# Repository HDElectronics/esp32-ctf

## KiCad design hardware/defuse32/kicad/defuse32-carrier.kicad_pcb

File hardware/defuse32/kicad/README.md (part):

# Defuse32 carrier PCB, rev 3.1 (KiCad 10, 4 layers; schematic rev 2.1)

The carrier board sits on the case floor and connects to the six plates by ribbon cables. Rev 2 is an SMD board assembled by JLCPCB: ESP32-WROOM-32E module, USB-C programming port with a CH340C, two MCP23017 expanders, LIS3DH tilt sensor, push-push microSD, WS2812 buffer, buzzer driver and one keyed IDC box header per plate. The source of truth is [`../SPEC.md`](../SPEC.md), section "Rev 2 carrier (2026-10-23)", plus the sections it keeps: ESP32 pin map, MCP23017 allocation (rev 1b), WS2812 chain, I2C addresses and the plate signal sets (rev 1 Jn_B table).

**Status (2026-11-25): rev 3.1, the standards pass of rev 3 (section "Standards pass (2026-11-25)"), with schematic rev 2.1 (Q1 SS8050, R7 330 Ω, new R21 WS_DATA pull-down and R22 SD CMD pull-up, owner-approved). Not ordered yet. Rev 3 (2026-10-24, commit 2b482c1): re-routed on 4 layers (JLCPCB JLC04161H-7628) and finished: GND pours on both outer layers stitched into two solid GND planes, 1.0 mm silkscreen beside every part (nothing on the bottom), 3D models for every part; JLCPCB fabrication and assembly files in `out/jlcpcb/`.** Rev 3 changed copper and silkscreen only (section "Rev 3"); rev 3.1 also adds R21 / R22 to the routed board (no regeneration).

| Check | Result |
|---|---|
| `kicad-cli sch erc --severity-all` | 0 errors, 0 warnings |
| `kicad-cli pcb drc --severity-all --schematic-parity --refill-zones --all-track-errors` | 0 violations, 0 unconnected items, 0 schematic parity issues (JLCPCB 4-layer minimums and custom rules; silk_over_copper, silk_overlap, silk_edge_clearance are errors; silk clearance 0.15 mm, text >= 1.0 mm / 0.15 mm) |
| `gen/check_netlist.py` | OK: netlist and board pads match `design.py`, plus the SPEC pin map, MCP23017 allocation, IDC pinout rule, rails, AMS1117 capacitors, outline, holes, U1 antenna beyond the edge and net classes |
| `gen/pcb_audit.py` (finish audit, `out/audit.json`; routing checks tightened 2026-11-25) | silkscreen: 0 violations, 0 warnings, no hidden part reference (R16-R19 share the label "R16-19"; the fiducials FID1-FID3 are board-only and print no reference); 3D: every part has a model; routing: 0 right angles, **7 jogs**, 23 tight corners, 1 hairpin, 0 cap-only joins, 0 stray segments (rev 3 by the same count: 23 / 30 / 3 / 7 / 10; every one left has its measured reason under "Standards pass"); copper: 66 narrow voids (129.3 mm2), none can take a usable stitching via |
| `gen/std_audit.py` (standards measurements, `out/std_audit.json`) | 0 off-angle segments, 0 acute junctions, 0 vias in SMD pads, every fast-net layer change within 2 mm of a GND via, LCSC on all 68 fitted parts; copper 0.5 mm or more from the two long edges (J11's shell pads 0.475 mm); 5V F1 -> U5 / U6 34 / 48 mΩ (network solve) |

Rev 1b (THT, DevKitC socket, 190 x 140 mm, routed) is in git, tag `carrier-rev1b`.

Changes against SPEC "Rev 2 carrier" made on 2026-10-23 (SPEC.md not edited yet): **U5 (3V3P) is an AMS1117-3.3** instead of the AP2112K-3.3 (see Power), and the microSD card-detect level is now documented (**low = card present**; firmware `CONFIG_D32_SD_DET_ACTIVE_HIGH=n`).

## Rev 3: four layers (2026-10-23/24)

The owner reviewed rev 2.1 and asked for: no gaps left between tracks (grounded copper), no 90° corners, 3D models for every part, labels aligned and right next to their part (R4 with R6 R9 R5; C6 and R20 beside, not off a corner), 4 layers allowed, and JLCPCB's capabilities respected (with the JLCPCB Tools plugin's conventions). Rev 3 keeps placement, schematic, netlist and pin map, and re-routes the board on 4 layers.

| | rev 2.1 (2 layers) | rev 3 (4 layers) |
|---|---|---|
| Stack-up | 2 layers, 1.6 mm | JLC04161H-7628, 1.6 mm: signals + GND pour / GND plane / GND plane / signals + GND pour |
| Jogs (audit) | 49 | **9** (110 straight out of Freerouting) |
| 90° corners (audit) | 12 | **0** |
| Copper voids >= 0.5 mm2 (audit) | 83, 159 mm2 | 60, 137.8 mm2 |
| ... of which a stitching via fits | 0 | 2 by the audit's test, neither usable (below) |
| Silkscreen violations / warnings (rev 3 audit, text >= 1.0 mm) | 3 / 18 (two 45° labels, R4 out of its row; 11 ambiguous, 7 far) | **0 / 0** |
| Reference size | 0.8 mm / 0.15 mm | 1.0 mm / 0.15 mm (JLCPCB's minimum height) |
| Top-side parts labelled on the bottom silkscreen | 7 | **0** |
| Callouts (label + leader) | 3 | 10 |
| Hidden references | none | none (R16-R19 share one label, "R16-19") |
| Parts without a 3D model | 4 (J7, SW1, SW2, F1) | **0** |
| Vias | 427 (275 GND) | 524 (353 GND: 45 fan-out, 144 island, 138 grid, 11 return, 15 pre-route) |
| Track length | 5978 mm, 1272 segments | 6116 mm (F.Cu 3243, B.Cu 2873), 1442 segments |
| USB D+ / D- | 15.6 mm (2 vias) / 14.8 mm, 0.8 mm apart | 15.4 mm (2 vias) / 14.8 mm, 0.6 mm apart, no double bend |
| Decoupling (cap pad to supply pad) | table below | unchanged, every cap within 3 mm |
| KiCad DRC (all severities, parity, refill) / ERC / check_netlist | 0 / 0 / 0, 0, OK | 0 / 0 / 0 (JLCPCB rules), 0, OK |

**Stack-up (option B of the pcb-layout-pro skill, `references/four-layer.md`).** JLCPCB JLC04161H-7628, 1.6 mm: L1 F.Cu signals + power + GND pour, L2 In1.Cu solid GND plane, L3 In2.Cu solid GND plane, L4 B.Cu signals + power + GND pour; no tracks on L2/L3. Option A (power areas on L3) was the default; B was chosen because:

- the three rails (5V, 3V3, 3V3P) each reach the whole board and meet on adjacent pins of every box header (pin 1 = 5V, pin 3 = 3V3P), so L3 cannot be split into areas; it would become a layer of 0.6 mm power tracks that crossed each other and cut the plane under every L4 signal;
- in JLC04161H-7628 L2 and L3 are 1.065 mm apart (core), so a power plane on L3 would add only ~4 pF/cm2 of plane capacitance; the decoupling caps do that job anyway;
- with B every signal layer has an unbroken GND plane 0.21 mm away and a layer change stays GND-to-GND (a GND via next to it carries the return); power currents are small (≤ 1 A on 5V), 0.6 mm tracks are plenty.

**JLCPCB rules (no extra cost).** Board minimums and the `.kicad_dru` follow JLCPCB's 4-layer capability page (read 2026-10-23, numbers in the skill's `references/jlcpcb.md`), at values that stay inside the standard price: no hole under 0.2 mm, 0.2 mm holes only with ≥ 0.45 mm vias (GND fan-out and stitching vias 0.45/0.2; signal and power vias 0.6/0.3), via hole to via hole 0.25 mm, pad hole to pad hole 0.45 mm, PTH hole to track 0.28 mm, inner PTH hole to copper 0.3 mm, track/space ≥ 0.1 mm (the net classes keep 0.2/0.2 and 0.6/0.25), copper 0.3 mm from the edge, silkscreen text ≥ 1.0 mm / 0.15 mm. Order options: 4 layers, JLC04161H-7628, 1 oz / 0.5 oz, impedance control off, tented vias (`out/jlcpcb/README.md`).

**Routing.** Same pre-routes as rev 2 (USB, LIS3DH fan-out, U1 decoupling, box-header GND stubs), now with 45° corners everywhere, and D+/D- leaving U9 on the line of J7's pads, so the pair runs straight with no 0.2 mm double bend. GND fan-out: 45 pads, 0.45/0.2 vias into the planes. Freerouting 2.4.1 routes F.Cu and B.Cu (the DSN has GND planes on all four layers, In1/In2 as plane layers), with its optimizer off: in 2.4.1 the optimizer stage starts from an older, less routed board (rev 3 runs: 1 connection open after routing, 23 after the optimizer). The one connection it left open (the LIS3DH supply group to the rest of 3V3P) is routed by `route_prep.py maze` (two-layer octilinear A*, 5 segments, no via). Session: `out/defuse32-carrier.ses`.

**Finish (`gen/polish.py all`, extended for rev 3).**

1. *Jogs: 110 -> 9.* After the rev 2.1 moves (extend, slide, push aside, corridor re-route), every run that still has a jog is ripped up and re-routed in jog-free mode: route_prep's maze search may not turn back to the heading it had before a 45° run shorter than 2.2 mm (that return is the audit's jog: offset < 1.5 mm, slanted part < 3 mm), with no 90° turn, on its own layer or over both outer layers with at most two vias; runs with T-junctions take their branches along; a run with no jog-free path gets the runs of other nets beside it ripped up as well and all of them routed again the same way. GND fan-out vias in the way are rebuilt round their pad (GND reaches the planes from anywhere). A last local pass catches jogs the re-routes leave behind (BUZZ- next to the U2_GPA7 via, fixed by moving that via down); IR between C1's pads went with its neighbours MCP_INT, SCL, T4 and T6 ripped up. Each change is checked by the exact clearance model and by KiCad's DRC before it is kept.
2. *Corners: 0 left.* Every 90° corner becomes two 45° bends (cut back up to 1 mm, or merged into the next 45° segment); where a track joins the corner (T-junction, e.g. at SW1) the joining track slides onto the new 45° segment, or the run is re-routed without the turn.
3. *Copper.* GND pours on F.Cu and B.Cu, solid planes on In1/In2 (clearance 0.2 mm, minimum width 0.2 mm, thermal reliefs 0.3 / 0.5 mm, island removal always). Every outer-layer pour piece is stitched into the planes (144 island vias), a 5 mm grid adds 138 more, and 11 GND vias sit next to the layer changes of the fast nets (USB, SPI, WS2812 data; none fits next to the SCK via at (78.95, 55.84)). No floating copper. **60 voids remain (137.8 mm2)**, all strips between tracks too narrow for a via with its clearances; the audit's via-fit test passes two of them, neither usable: one lies under the C10 label (no via under text), the other is the gap between two U7 pins (0.73 mm), where the 0.2 mm pad clearances leave no room.
4. *Silkscreen.* One size, 1.0 mm / 0.15 mm, 0 or 90°, beside one side of the part (≥ 40 % overlap with its span, never off a corner), ≤ 1 mm away, outside every courtyard, never over a via; rows aligned in part order (R6 R9 R5 R4 on one line; C6 and R20 right beside their parts); none on the bottom silkscreen. Parts with no free spot beside them get a callout: label a short way off with a 0.15 mm leader to the part (U8, R14, R15, R11, C14, C19, C4, R8, C18, C2). R16-R19 (boxed in by U5, J5, C19/C1 and J11) share one label, "R16-19", beside their row. Header names are one line along the header's long side: "J1  M1 RADIO" ... "J6  M6 SENSORS" (J5 reads "M5 PROBE  J5": the space right of it is R16-19's). Board legend, revision and the JLCPCB order-number spot are kept.
5. *3D models.* J7 (HRO TYPE-C-31-M-12, C165948), SW1/SW2 (XKB TS-1187A, C318884) and F1 (1812 PTC, C18198338) had no model in KiCad's library: `gen/fetch_3d.py` fetches the LCSC/EasyEDA STEP models with easyeda2kicad 1.0.1 into `3d/` (git-ignored: licence unclear for this MIT repository) and works out where each sits on our footprint by matching the pad sets (drilled pegs and shell legs weigh 5x). easyeda2kicad 1.0.1 places STEP models wrongly whenever EasyEDA's model origin is off the footprint origin or the model is rotated (it bakes the offset into the VRML only, before KiCad's rotation): J7 came out 2.4 mm too far toward its pads; fetch_3d.py corrects it (offsets in `gen/models3d.json`, applied by `gen_pcb.py`). Checked on renders: USB-C opening flush with the right edge, microSD slot on the bottom edge, buttons and fuse on their pads. F1's EasyEDA land pattern has a 3.7 mm pad pitch against KiCad's 4.275 mm, so the body is centred on our pads.

**What is left and why.** The 9 jogs, each a single 45° pair (`/usr/bin/python3 gen/polish.py jogs` lists them with what keeps them):

| Net, layer | At (mm) | Step | Kept by |
|---|---|---|---|
| 5V, B.Cu | (6.09, 32.27) | 0.20 | the ENC_SW via beside it; a T-junction pins the run |
| 5V, B.Cu | (11.57, 47.83) | 0.42 | the IR and SERVO_SIG vias on either side |
| SCL, B.Cu | (15.16, 63.79) | 1.21 | J4 pads 3 and 4, the SDA track and a GND via |
| SCK, B.Cu | (39.87, 17.27) | 1.01 | the pads / vias it joins leave no straight line |
| SCK, B.Cu | (50.88, 45.06) | 1.32 | crosses the BUZZ, LDO3, SDA and U2_GPA7 runs |
| 3V3, F.Cu | (79.36, 42.74) | 0.67 | T-junction at U7's supply pins |
| SIM4, F.Cu | (67.33, 27.94) | 1.25 | C3's pads and the 3V3P / SD_DET tracks |
| U0RXD, F.Cu | (70.59, 44.25) | 0.60 | between C7 pad 2 and U6 pad 2 |
| U0RXD, F.Cu | (72.63, 46.74) | 0.32 | the U0TXD via and the 3V3 track |

Each was tried with the local moves, the jog-free maze (12 mm window, two layers) and the rip-up of up to eight neighbouring runs; removing them needs a hand re-route of the crossing runs. The copper voids are the narrow strips above; the one fast-net layer change without a GND via beside it is SCK at (78.95, 55.84) (the return current changes plane, GND1 to GND2, at the nearest stitching via instead).

## Standards pass (2026-11-25): board rev 3.1, schematic rev 2.1

The owner asked to check the board and correct every error "with the skills and the standard used on the AirQuality project" (its `docs/hw/layout.md` §15 / §15.1: an audit against IPC-2221B class 2, IPC-2152, JLCPCB's capabilities, USB 2.0 / Type-C and the vendor guides, then scripted fixes with no part moved). Checked: IPC-2221B spacing / edge / annular ring, IPC-2152 track current, JLCPCB 4-layer and PCBA rules (fiducials, rails, component-to-edge, overhang, Economic vs Standard, CPL rotations), a power budget against F1, both AMS1117 and the USB source, USB 2.0 / Type-C (CC, VBUS capacitance, D+/D-, ESD, shield), the ESP32-WROOM-32E datasheet and Espressif's hardware design guidelines, every IC against its datasheet, protection of the plate signals, return paths, routing quality, copper voids, silkscreen and markings, schematic hygiene, the kicad-happy analyzers, Codex's independent audit (D01-D22) and a second review (Fable, F01-F09). Measurements: `gen/std_audit.py` (new, read-only, port of AirQuality's `std_audit.py`) and `gen/pcb_audit.py`. Fixes: `gen/std_fixes.py` (new; runs after `gen/polish.py all`). No existing footprint moved, rotated or swapped (one exception since: on 2026-11-26 the owner asked for the USB-C receptacle J7 to stand 0.6 mm past the edge, "USB-C receptacle out of the edge" below). The spec side is in [`../SPEC.md`](../SPEC.md), section "Rev 3.1 carrier, schematic rev 2.1". A read-only final check of that pass (N01-N12) found errors in it; round 2, the same day, applies its fixes, counts jogs and corners honestly and removes what can be removed ("Round 2" below). The numbers in this section are the final ones.

**Schematic rev 2.1 (owner-approved, 2026-11-25; not the 2-layer *board* rev 2.1 of October).** Two changes, both from the review, everything else in the schematic unchanged:
- Buzzer driver: **Q1 MMBT3904 -> SS8050** (C2150, JSCJ, SOT-23, Basic; same pins 1 B / 2 E / 3 C, JSCJ datasheet p.1; 1.5 A, hFE 200-350) and **R7 1 k -> 330 Ω** (C23138, as R1): 7.6 mA base current saturates Q1 at the 120-310 mA a 16-42 Ω magnetic buzzer takes at 5 V (the MMBT3904 is rated 200 mA). Same footprints, positions and copper.
- **R21 10 k WS_DATA -> GND** (C25804) at (44.30, 35.90), below the GPIO25 -> U4 pin 2 track: GPIO25 is high-Z during reset and U4's OE is tied low, so the buffer input was undefined at power-up. **R22 10 k MOSI -> 3V3P** (C25804) at (71.30, 64.50), left of J11: Espressif's "SD pull-up requirements" ask for 10 k on CMD (MOSI) as on DAT0-2, also in SPI mode. Both spots come from a search (courtyard clear, pads clear of other-net copper, nearest copper of both nets); the review's spots were not usable after the 5V feed (R22) or took C15's label place (R21). Coordinates are board mm from the top-left corner. `gen/std_fixes.py` (`new_parts`) adds them to the routed board (no board regeneration): R21 pad 1 joins the WS_DATA track with one 45° segment that meets it at 90° (0.9 mm), pad 2 the GND track below it; R22 pad 1 drops to the B.Cu 3V3P track through a via beside the pad, pad 2 runs on F.Cu to the MOSI via at (67.81, 66.81) (4.1 mm). Both carry LCSC / MPN fields from `design.py`, KiCad 3D models and a 1.0 mm label placed by the silkscreen rules.

| Check | rev 3 (commit 2b482c1) | rev 3.1 before round 2 | rev 3.1 (final) |
|---|---|---|---|
| KiCad DRC (all severities, `--schematic-parity --refill-zones --all-track-errors`) | 0 / 0 / 0 | 0 / 0 / 0 | 0 / 0 / 0 |
| ERC / `check_netlist.py` | 0 / OK | 0 / OK | 0 / OK (section 8 checks the schematic rev 2.1 parts; fiducials are board-only, no net) |
| Jogs (`pcb_audit.py`, pieces under 0.1 mm merged first) | **23** (the old audit showed 9: a step behind a router ring was not seen) | 15 (the old audit showed 14) | **7** (table below) |
| Tight corners (a turn of 90° or more within 0.45 mm) / hairpins (135° or more) | 30 / 3 | 32 / 3 | **23 / 1** (below) |
| Track ends joined by their round cap only / stray segments inside a pad or via / overlapping segments | 7 / 10 / 1 | 9 / 11 / 0 | **0 / 0 / 0** |
| Tracks entering a pad through its corner or at its rim (warning) | 28 | 35 | 11 (SMD pads; the 21 track ends that stopped on the rim of a header pad now end 0.15 mm or more inside it) |
| Right angles / off-angle segments (> 1° off 0/45/90) / acute junctions (`std_audit.py`) | 0 / 32 / 6 (3 inside a pad) | 0 / 0 / 0 | **0 / 0 / 0** |
| Segments < 0.1 mm | 155 on 29 nets | 93 on 24 nets (13 hooks of 4-6 pieces left: 12 corner arcs and a ring on IR) | 65 on 19 nets |
| Vias in or touching SMD pads | 7 | 0 | **0** |
| Fast-net layer changes with no GND via within 2.0 mm | 6 | 0 | **0** (largest left: SCK 1.92 mm, LDO4 1.80 mm, CS 1.76 mm) |
| 5V copper from F1 pad 2, network solve (1 oz, 25 °C) | U5 224 mΩ, U6 268, C1 207, J9 165, J4 188, J5 219 | U5 35, U6 48, C1 45, J9 56, J4 66, J5 69 | **U5 34 mΩ, U6 48, C1 41, J9 54, J4 66, J5 69** |
| 5V tracks | 0.6 mm | 29 segments (119 mm) at 0.8-1.2 mm | the same, and the C1 - U5 run 1.0 mm (was 0.6) |
| Regulator tab copper (SOT-223 pin 4) | pad only | F.Cu areas on U6 (3V3, 27.8 mm²) and U5 (3V3P, 36.4 mm²) | U6's area reaches down to the IO0 track (28.4 mm²); U5's is 34.2 mm² now that C19 / C2 pad 1 (and C8 pad 1 at U6) join through thermal reliefs; the tab pads stay solid |
| Under U8 LIS3DH (TN0018 §2.3, secondary source) | GND pour and vias | rule area: no pour, no vias inside the land ring | the same |
| Copper to the two long (100 mm) edges | pours 0.30 mm | pours 0.30 mm | **0.50 mm** on all four layers (V-cut rails possible); J11's shell pads 0.475 mm |
| Silkscreen violations / warnings / hidden part references (`pcb_audit.py`) | 0 / 0 / none | 0 / 0 / none | **0 / 0 / none** |
| Markings | references only | + EN, BOOT, OUT, G / + / S at J9, "rev 3.1  2026-11" | "S" on the same side of J9 as "G" and "+"; R21's label 0.25 mm further from R1; a leader from J11's label to the socket |
| Global fiducials | 0 | 3, centres 3.5-4.8 mm from the edges | 3, centres 3.9 mm or more from every edge (JLCPCB: 3.85 mm) |
| Edge stitching (points 1.5 mm inside the edge > 3 mm from a GND via) | 111 | 94 | 91 (left edge under U1 and bottom edge under J11: no via fits) |
| Copper voids >= 0.5 mm², each counted once (the audit lists a void once per zone that could fill it) | 60, 137.8 mm² | 72, 150.8 mm² | **66, 129.3 mm²** (3 pass the audit's via-fit test, none usable: below) |
| Vias / track length | 524 / 6116 mm | 538 / 6173 mm | 536 / 6168 mm (541 / 6173 mm after the J7 move of 2026-11-26) |
| BOM / CPL | | schematic rev 2.1 lines; C1 turned by 180° (wrong) | schematic rev 2.1 lines; rotations checked against each part's LCSC footprint: C1 0, J7 90, Q1-Q3 and U4 180 (`out/jlcpcb/README.md`) |

**What changed (copper, silkscreen and board-only items, `gen/std_fixes.py`; each step is checked with the exact clearance model and KiCad's DRC).**

- *5V feed (Codex D03).* F1 reached the regulators only round the board (267 mΩ to U6). A new 0.6 mm feed runs F1 pad 2 -> C6 / U5 (38 mm, 8 vias, through the gaps the relaxed maze found) and C6 -> C7 / U6 (16 mm, 4 vias, jog-free); the 5V tracks are then widened to 1.2 / 1.0 / 0.8 mm wherever clearances allow (never wider than the smallest SMD pad they meet). In the review's 1.5 A case the drop on the board path falls from ~0.4 V to ~0.08 V (U6 input ~4.6 V instead of ~4.3 V, above the AMS1117's 1.3 V maximum dropout).
- *Regulator tabs (D04).* Solid F.Cu areas on U6's (3V3) and U5's (3V3P) tab pads, priority over the GND pour, for heat spreading.
- *LIS3DH (D12).* A rule area under U8: no GND pour and no vias inside its land ring (ST's TN0018 §2.3 as cited by ST; TN0018 itself could not be fetched). Paste apertures unchanged (unverified guidance).
- *Routing.* The router's micro-loops (≥ 3 segments shorter than 0.3 mm folding back) collapse to the corner they stand for; that exposed 14 jogs the old audit had not counted. The polish jog tools then run with the pours lifted: 6 fixed for good; 7 maze re-routes only moved their step behind a new ring (collapsed again, see below). Two hand edits (SCL near J4, SCK bus near U2) replace runs the tools could not straighten. 32 off-angle segments (router remnants, 22.5° fan-out stubs) become 0/45/90; 6 acute junctions are rebuilt as 45° or square T's; the vias in or touching an SMD pad (GND fan-outs at C1, C2, C8, U2 pins 15 / 16, U3 pin 16; the MCP_INT via in R4 pad 2) move clear of the pad, with axial stubs; IR is re-routed round the moved R4 via.
- *Return vias (D17).* A GND via within 0.8-1.8 mm of each fast-net layer change that had none within 2 mm (CS x2, LDO2, LDO3, LDO4; LDI after the edits); the stitching vias in the way move.
- *Edge stitching.* 4 GND vias where the outer pours reach the edge more than 3 mm from a via.
- *Silkscreen (D21, D22).* EN beside SW1, BOOT beside SW2, OUT beside J10, G / + / S beside J9 pins 1-3, legend "rev 3.1  2026-11" (title block rev 3.1, 2026-11-25), JLCJLCJLCJLC kept. R21 / R22 labelled by the same rules (J11's label moves to the right of J11 to make room for R22's). Footprint silk widths unchanged (D20: widening them would make the DRC library-parity check report every footprint).
- *Fiducials (second review F02).* FID1 (3.9, 21.3), FID2 (90.3, 4.8), FID3 (94.8, 61.4) board mm from the top-left: KiCad `Fiducial_1mm_Mask2mm`, board-only (excluded from BOM and position files, no reference printed: a fiducial is not a part), centres 3.9 mm or more from every edge (JLCPCB asks for 3.85 mm from the panel edge), triangle across the board.
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
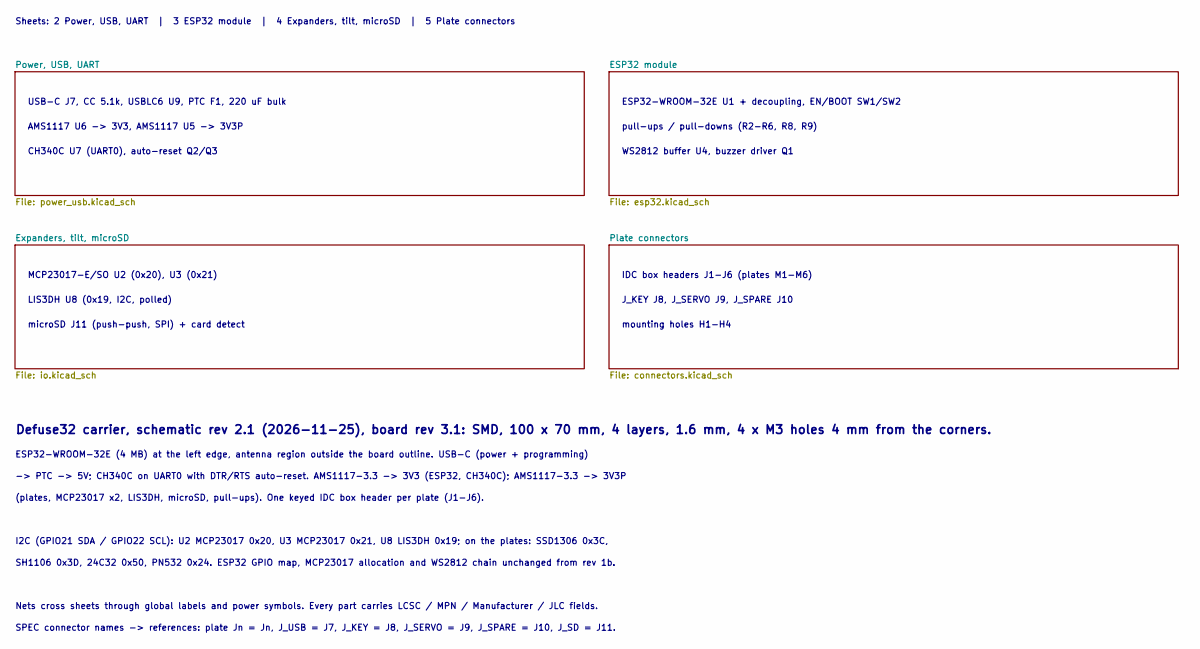
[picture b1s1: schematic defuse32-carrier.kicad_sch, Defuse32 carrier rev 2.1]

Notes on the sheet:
USB-C J7, CC 5.1k, USBLC6 U9, PTC F1, 220 uF bulk
AMS1117 U6 -> 3V3, AMS1117 U5 -> 3V3P
CH340C U7 (UART0), auto-reset Q2/Q3
ESP32-WROOM-32E U1 + decoupling, EN/BOOT SW1/SW2
pull-ups / pull-downs (R2-R6, R8, R9)
WS2812 buffer U4, buzzer driver Q1
MCP23017-E/SO U2 (0x20), U3 (0x21)
LIS3DH U8 (0x19, I2C, polled)
microSD J11 (push-push, SPI) + card detect
IDC box headers J1-J6 (plates M1-M6)
J_KEY J8, J_SERVO J9, J_SPARE J10
mounting holes H1-H4
Defuse32 carrier, schematic rev 2.1 (2026-11-25), board rev 3.1: SMD, 100 x 70 mm, 4 layers, 1.6 mm, 4 x M3 holes 4 mm from the corners.
ESP32-WROOM-32E (4 MB) at the left edge, antenna region outside the board outline. USB-C (power + programming)
-> PTC -> 5V; CH340C on UART0 with DTR/RTS auto-reset. AMS1117-3.3 -> 3V3 (ESP32, CH340C); AMS1117-3.3 -> 3V3P
(plates, MCP23017 x2, LIS3DH, microSD, pull-ups). One keyed IDC box header per plate (J1-J6).
I2C (GPIO21 SDA / GPIO22 SCL): U2 MCP23017 0x20, U3 MCP23017 0x21, U8 LIS3DH 0x19; on the plates: SSD1306 0x3C,
SH1106 0x3D, 24C32 0x50, PN532 0x24. ESP32 GPIO map, MCP23017 allocation and WS2812 chain unchanged from rev 1b.
Nets cross sheets through global labels and power symbols. Every part carries LCSC / MPN / Manufacturer / JLC fields.
SPEC connector names -> references: plate Jn = Jn, J_USB = J7, J_KEY = J8, J_SERVO = J9, J_SPARE = J10, J_SD = J11.
Sheets: 2 Power, USB, UART | 3 ESP32 module | 4 Expanders, tilt, microSD | 5 Plate connectors

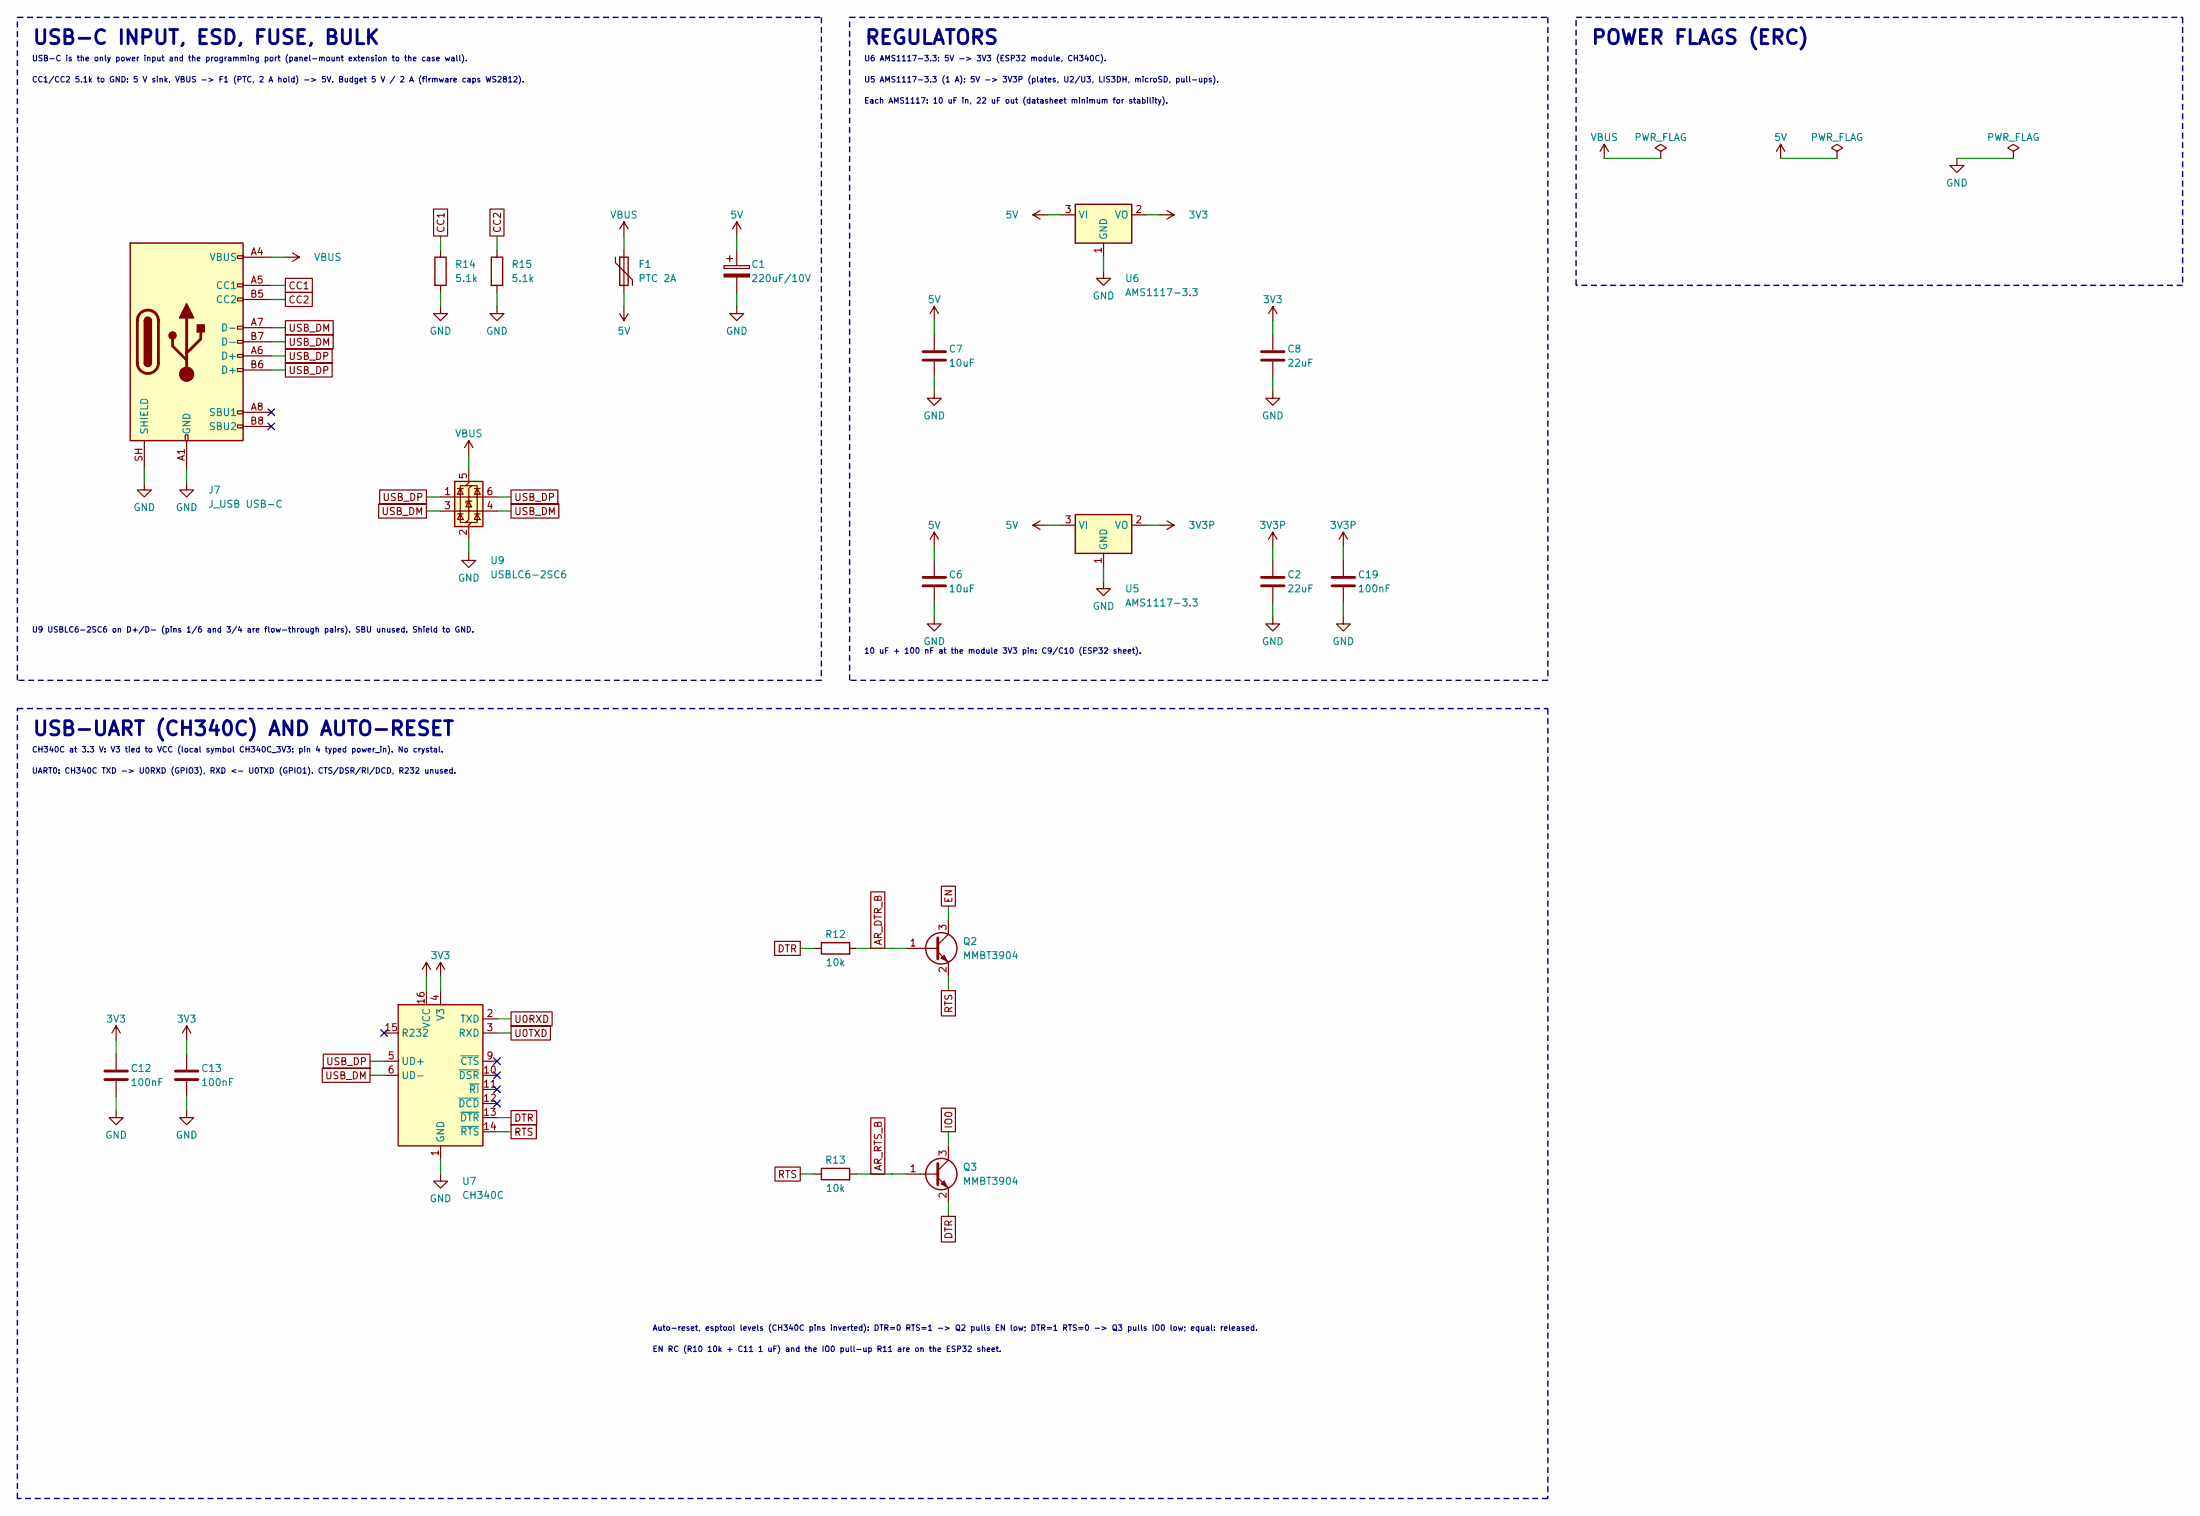
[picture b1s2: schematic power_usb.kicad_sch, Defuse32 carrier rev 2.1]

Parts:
C1: 220uF/10V; CP_Elec_6.3x5.4; MPN RVT1A221M0605; LCSC C72494
C2, C8: 22uF; C_0805_2012Metric; MPN CL21A226MAQNNNE; LCSC C45783
C6, C7: 10uF; C_0805_2012Metric; MPN CL21A106KAYNNNE; LCSC C15850
C12, C13, C19: 100nF; C_0603_1608Metric; MPN CC0603KRX7R9BB104; LCSC C14663
F1: PTC 2A; Fuse_1812_4532Metric; MPN 1812L200/8GR; LCSC C18198338
J7: J_USB USB-C; USB_C_Receptacle_HRO_TYPE-C-31-M-12_Edge; MPN TYPE-C-31-M-12; LCSC C165948
Q2, Q3: MMBT3904; SOT-23; MPN MMBT3904; LCSC C20526
R12, R13: 10k; R_0603_1608Metric; MPN 0603WAF1002T5E; LCSC C25804
R14, R15: 5.1k; R_0603_1608Metric; MPN 0603WAF5101T5E; LCSC C23186
U5, U6: AMS1117-3.3; SOT-223-3_TabPin2; MPN AMS1117-3.3; LCSC C6186
U7: CH340C; SOIC-16_3.9x9.9mm_P1.27mm; MPN CH340C; LCSC C84681
U9: USBLC6-2SC6; SOT-23-6; MPN USBLC6-2SC6; LCSC C7519

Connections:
3V3: C8.1, C12.1, C13.1, U6.2 (VO), U7.4 (V3), U7.16 (VCC); also elsewhere on the board
3V3P: C2.1, C19.1, U5.2 (VO); also elsewhere on the board
5V: C1.1, C6.1, C7.1, F1.2, U5.3 (VI), U6.3 (VI); also elsewhere on the board
AR_DTR_B: Q2.1 (B), R12.2
AR_RTS_B: Q3.1 (B), R13.2
CC1: J7.A5 (CC1), R14.1
CC2: J7.B5 (CC2), R15.1
DTR: Q3.2 (E), R12.1, U7.13 (~DTR)
EN: Q2.3 (C); also elsewhere on the board
GND: C1.2, C2.2, C6.2, C7.2, C8.2, C12.2, C13.2, C19.2, J7.A1 (GND), J7.A12 (GND), J7.B1 (GND), J7.B12 (GND), J7.SH (SHIELD), R14.2, R15.2, U5.1 (GND), U6.1 (GND), U7.1 (GND), U9.2 (GND); also elsewhere on the board
IO0: Q3.3 (C); also elsewhere on the board
RTS: Q2.2 (E), R13.1, U7.14 (~RTS)
U0RXD: U7.2 (TXD); also elsewhere on the board
U0TXD: U7.3 (RXD); also elsewhere on the board
USB_DM: J7.A7 (D-), J7.B7 (D-), U7.6 (UD-), U9.3 (I/O2), U9.4 (I/O2)
USB_DP: J7.A6 (D+), J7.B6 (D+), U7.5 (UD+), U9.1 (I/O1), U9.6 (I/O1)
VBUS: F1.1, J7.A4 (VBUS), J7.A9 (VBUS), J7.B4 (VBUS), J7.B9 (VBUS), U9.5 (VBUS)

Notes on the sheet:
USB-C INPUT, ESD, FUSE, BULK
USB-C is the only power input and the programming port (panel-mount extension to the case wall).
CC1/CC2 5.1k to GND: 5 V sink. VBUS -> F1 (PTC, 2 A hold) -> 5V. Budget 5 V / 2 A (firmware caps WS2812).
U9 USBLC6-2SC6 on D+/D- (pins 1/6 and 3/4 are flow-through pairs). SBU unused. Shield to GND.
REGULATORS
U6 AMS1117-3.3: 5V -> 3V3 (ESP32 module, CH340C).
U5 AMS1117-3.3 (1 A): 5V -> 3V3P (plates, U2/U3, LIS3DH, microSD, pull-ups).
Each AMS1117: 10 uF in, 22 uF out (datasheet minimum for stability).
10 uF + 100 nF at the module 3V3 pin: C9/C10 (ESP32 sheet).
POWER FLAGS (ERC)
USB-UART (CH340C) AND AUTO-RESET
CH340C at 3.3 V: V3 tied to VCC (local symbol CH340C_3V3: pin 4 typed power_in). No crystal.
UART0: CH340C TXD -> U0RXD (GPIO3), RXD <- U0TXD (GPIO1). CTS/DSR/RI/DCD, R232 unused.
Auto-reset, esptool levels (CH340C pins inverted): DTR=0 RTS=1 -> Q2 pulls EN low; DTR=1 RTS=0 -> Q3 pulls IO0 low; equal: released.
EN RC (R10 10k + C11 1 uF) and the IO0 pull-up R11 are on the ESP32 sheet.

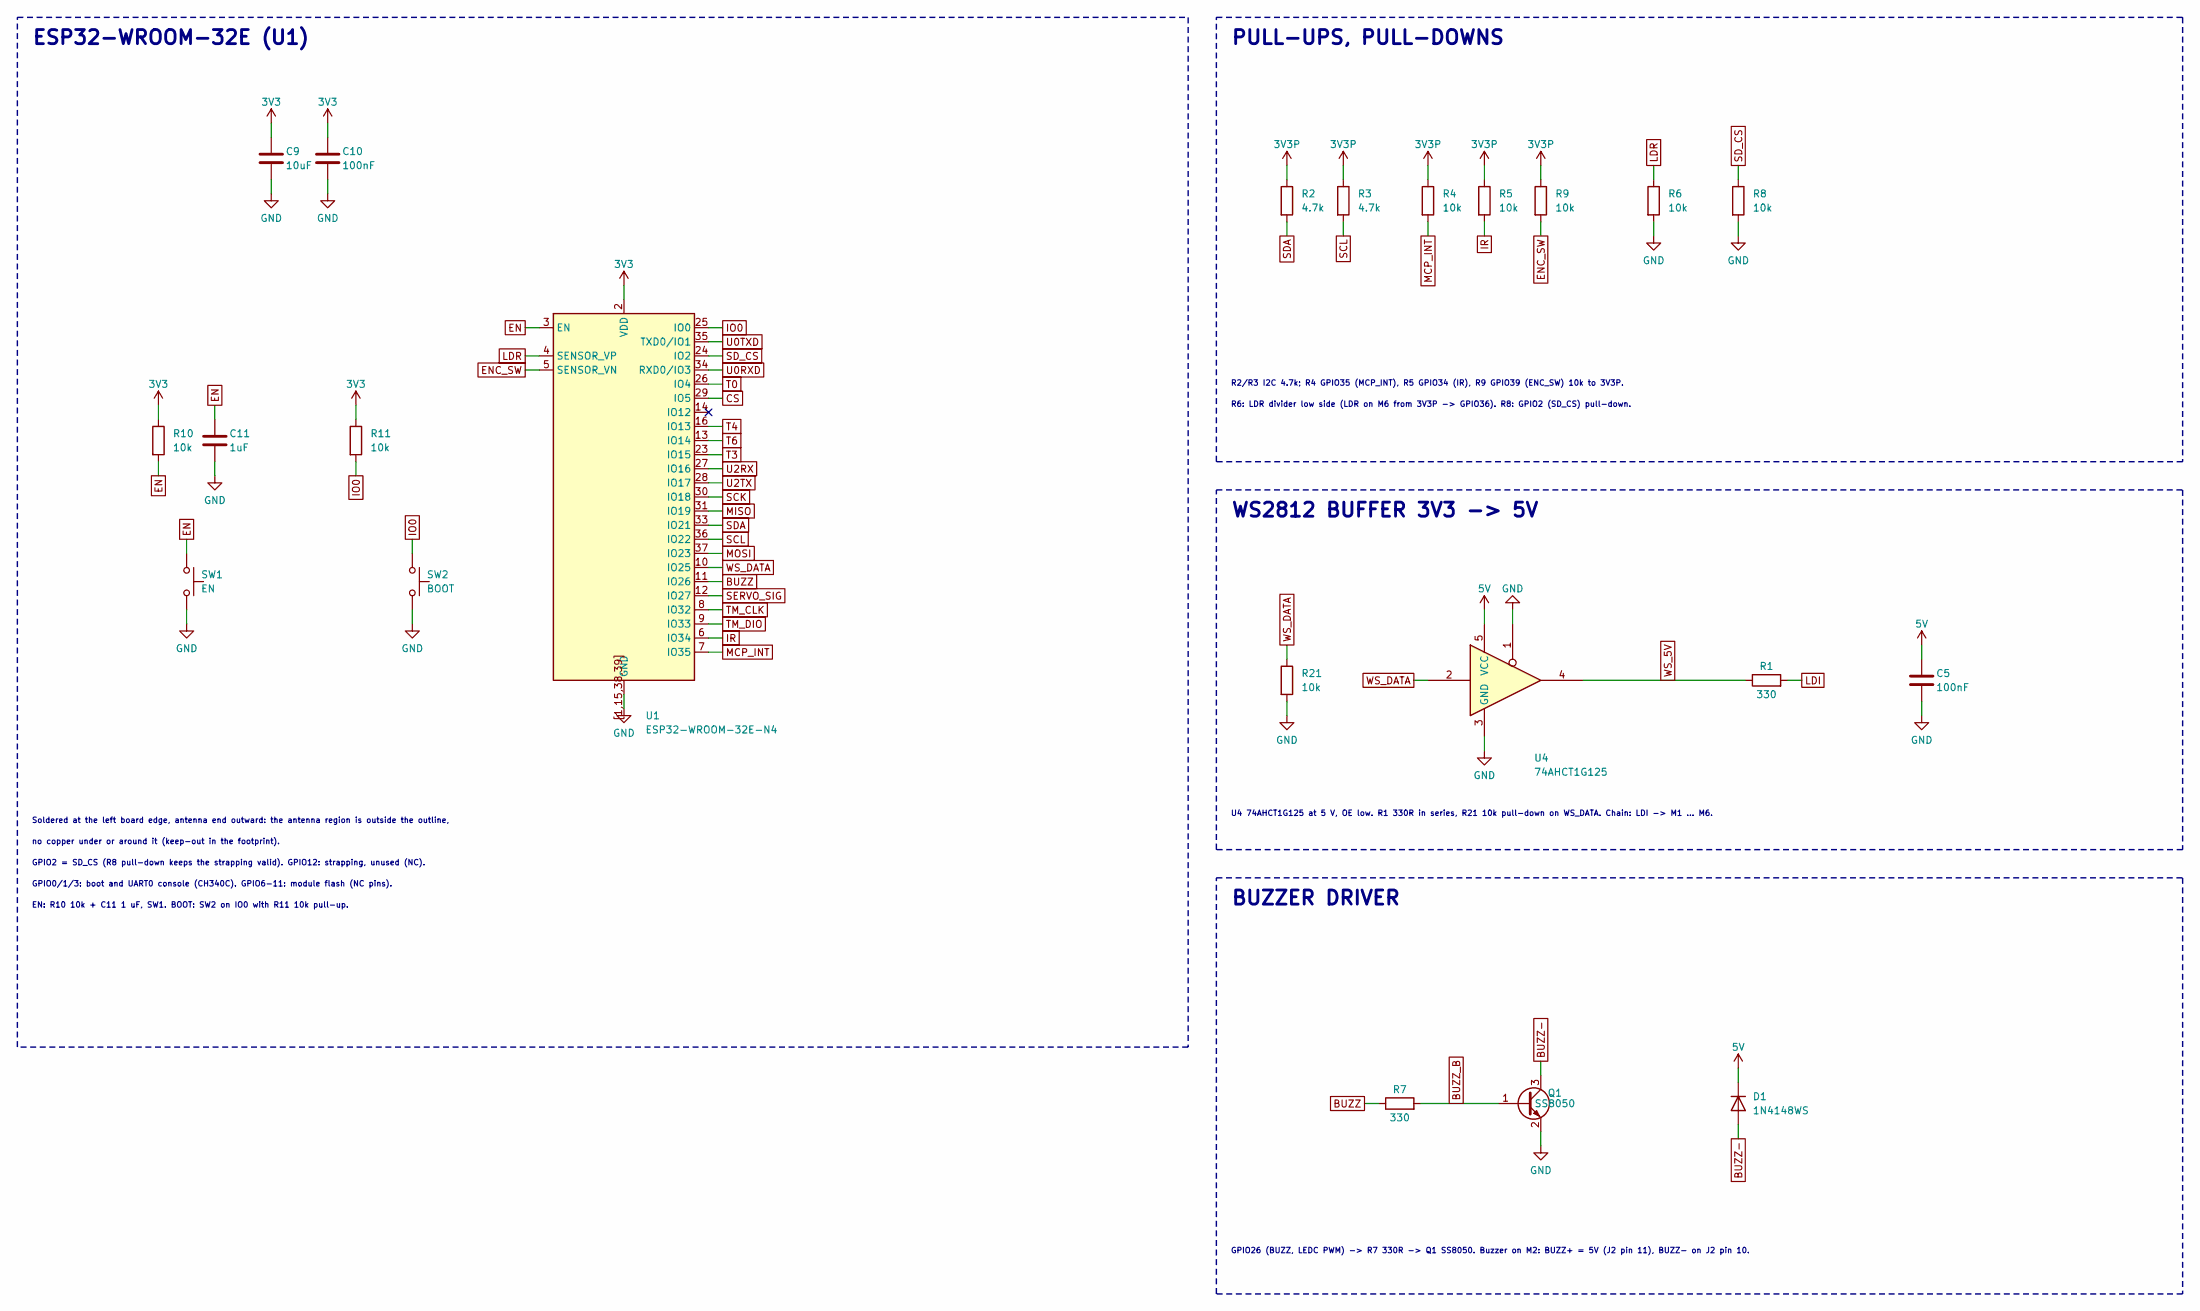
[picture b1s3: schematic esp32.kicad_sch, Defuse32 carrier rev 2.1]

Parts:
C5, C10: 100nF; C_0603_1608Metric; MPN CC0603KRX7R9BB104; LCSC C14663
C9: 10uF; C_0805_2012Metric; MPN CL21A106KAYNNNE; LCSC C15850
C11: 1uF; C_0603_1608Metric; MPN CL10A105KB8NNNC; LCSC C15849
D1: 1N4148WS; D_SOD-323; MPN 1N4148WS; LCSC C2128
Q1: SS8050; SOT-23; MPN SS8050(RANGE:200-350); LCSC C2150
R1, R7: 330; R_0603_1608Metric; MPN 0603WAF3300T5E; LCSC C23138
R2, R3: 4.7k; R_0603_1608Metric; MPN 0603WAF4701T5E; LCSC C23162
R4, R5, R6, R8, R9, R10, R11, R21: 10k; R_0603_1608Metric; MPN 0603WAF1002T5E; LCSC C25804
SW1: EN; SW_Push_1P1T_XKB_TS-1187A; MPN TS-1187A-B-A-B; LCSC C318884
SW2: BOOT; SW_Push_1P1T_XKB_TS-1187A; MPN TS-1187A-B-A-B; LCSC C318884
U1: ESP32-WROOM-32E-N4; ESP32-WROOM-32E_JLC; MPN ESP32-WROOM-32E-N4; LCSC C701341
U4: 74AHCT1G125; SOT-23-5; MPN SN74AHCT1G125DBVR; LCSC C7484

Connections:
3V3: C9.1, C10.1, R10.1, R11.1, U1.2 (VDD); also elsewhere on the board
3V3P: R2.1, R3.1, R4.1, R5.1, R9.1; also elsewhere on the board
5V: C5.1, D1.1 (K), U4.5 (VCC); also elsewhere on the board
BUZZ: R7.1, U1.11 (IO26)
BUZZ-: D1.2 (A), Q1.3 (C); also elsewhere on the board
BUZZ_B: Q1.1 (B), R7.2
CS: U1.29 (IO5); also elsewhere on the board
EN: C11.1, R10.2, SW1.1, U1.3 (EN); also elsewhere on the board
ENC_SW: R9.2, U1.5 (SENSOR_VN); also elsewhere on the board
GND: C5.2, C9.2, C10.2, C11.2, Q1.2 (E), R6.2, R8.2, R21.2, SW1.2, SW2.2, U1.1, U1.15, U1.38, U1.39, U1.[1,15,38,39] (GND), U4.1, U4.3 (GND); also elsewhere on the board
IO0: R11.2, SW2.1, U1.25 (IO0); also elsewhere on the board
IR: R5.2, U1.6 (IO34); also elsewhere on the board
LDI: R1.2; also elsewhere on the board
LDR: R6.1, U1.4 (SENSOR_VP); also elsewhere on the board
MCP_INT: R4.2, U1.7 (IO35); also elsewhere on the board
MISO: U1.31 (IO19); also elsewhere on the board
MOSI: U1.37 (IO23); also elsewhere on the board
SCK: U1.30 (IO18); also elsewhere on the board
SCL: R3.2, U1.36 (IO22); also elsewhere on the board
SDA: R2.2, U1.33 (IO21); also elsewhere on the board
SD_CS: R8.1, U1.24 (IO2); also elsewhere on the board
SERVO_SIG: U1.12 (IO27); also elsewhere on the board
T0: U1.26 (IO4); also elsewhere on the board
T3: U1.23 (IO15); also elsewhere on the board
T4: U1.16 (IO13); also elsewhere on the board
T6: U1.13 (IO14); also elsewhere on the board
TM_CLK: U1.8 (IO32); also elsewhere on the board
TM_DIO: U1.9 (IO33); also elsewhere on the board
U0RXD: U1.34 (RXD0/IO3); also elsewhere on the board
U0TXD: U1.35 (TXD0/IO1); also elsewhere on the board
U2RX: U1.27 (IO16); also elsewhere on the board
U2TX: U1.28 (IO17); also elsewhere on the board
WS_5V: R1.1, U4.4
WS_DATA: R21.1, U1.10 (IO25), U4.2

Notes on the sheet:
ESP32-WROOM-32E (U1)
Soldered at the left board edge, antenna end outward: the antenna region is outside the outline,
no copper under or around it (keep-out in the footprint).
GPIO2 = SD_CS (R8 pull-down keeps the strapping valid). GPIO12: strapping, unused (NC).
GPIO0/1/3: boot and UART0 console (CH340C). GPIO6-11: module flash (NC pins).
EN: R10 10k + C11 1 uF, SW1. BOOT: SW2 on IO0 with R11 10k pull-up.
PULL-UPS, PULL-DOWNS
R2/R3 I2C 4.7k; R4 GPIO35 (MCP_INT), R5 GPIO34 (IR), R9 GPIO39 (ENC_SW) 10k to 3V3P.
R6: LDR divider low side (LDR on M6 from 3V3P -> GPIO36). R8: GPIO2 (SD_CS) pull-down.
WS2812 BUFFER 3V3 -> 5V
U4 74AHCT1G125 at 5 V, OE low. R1 330R in series, R21 10k pull-down on WS_DATA. Chain: LDI -> M1 ... M6.
BUZZER DRIVER
GPIO26 (BUZZ, LEDC PWM) -> R7 330R -> Q1 SS8050. Buzzer on M2: BUZZ+ = 5V (J2 pin 11), BUZZ- on J2 pin 10.

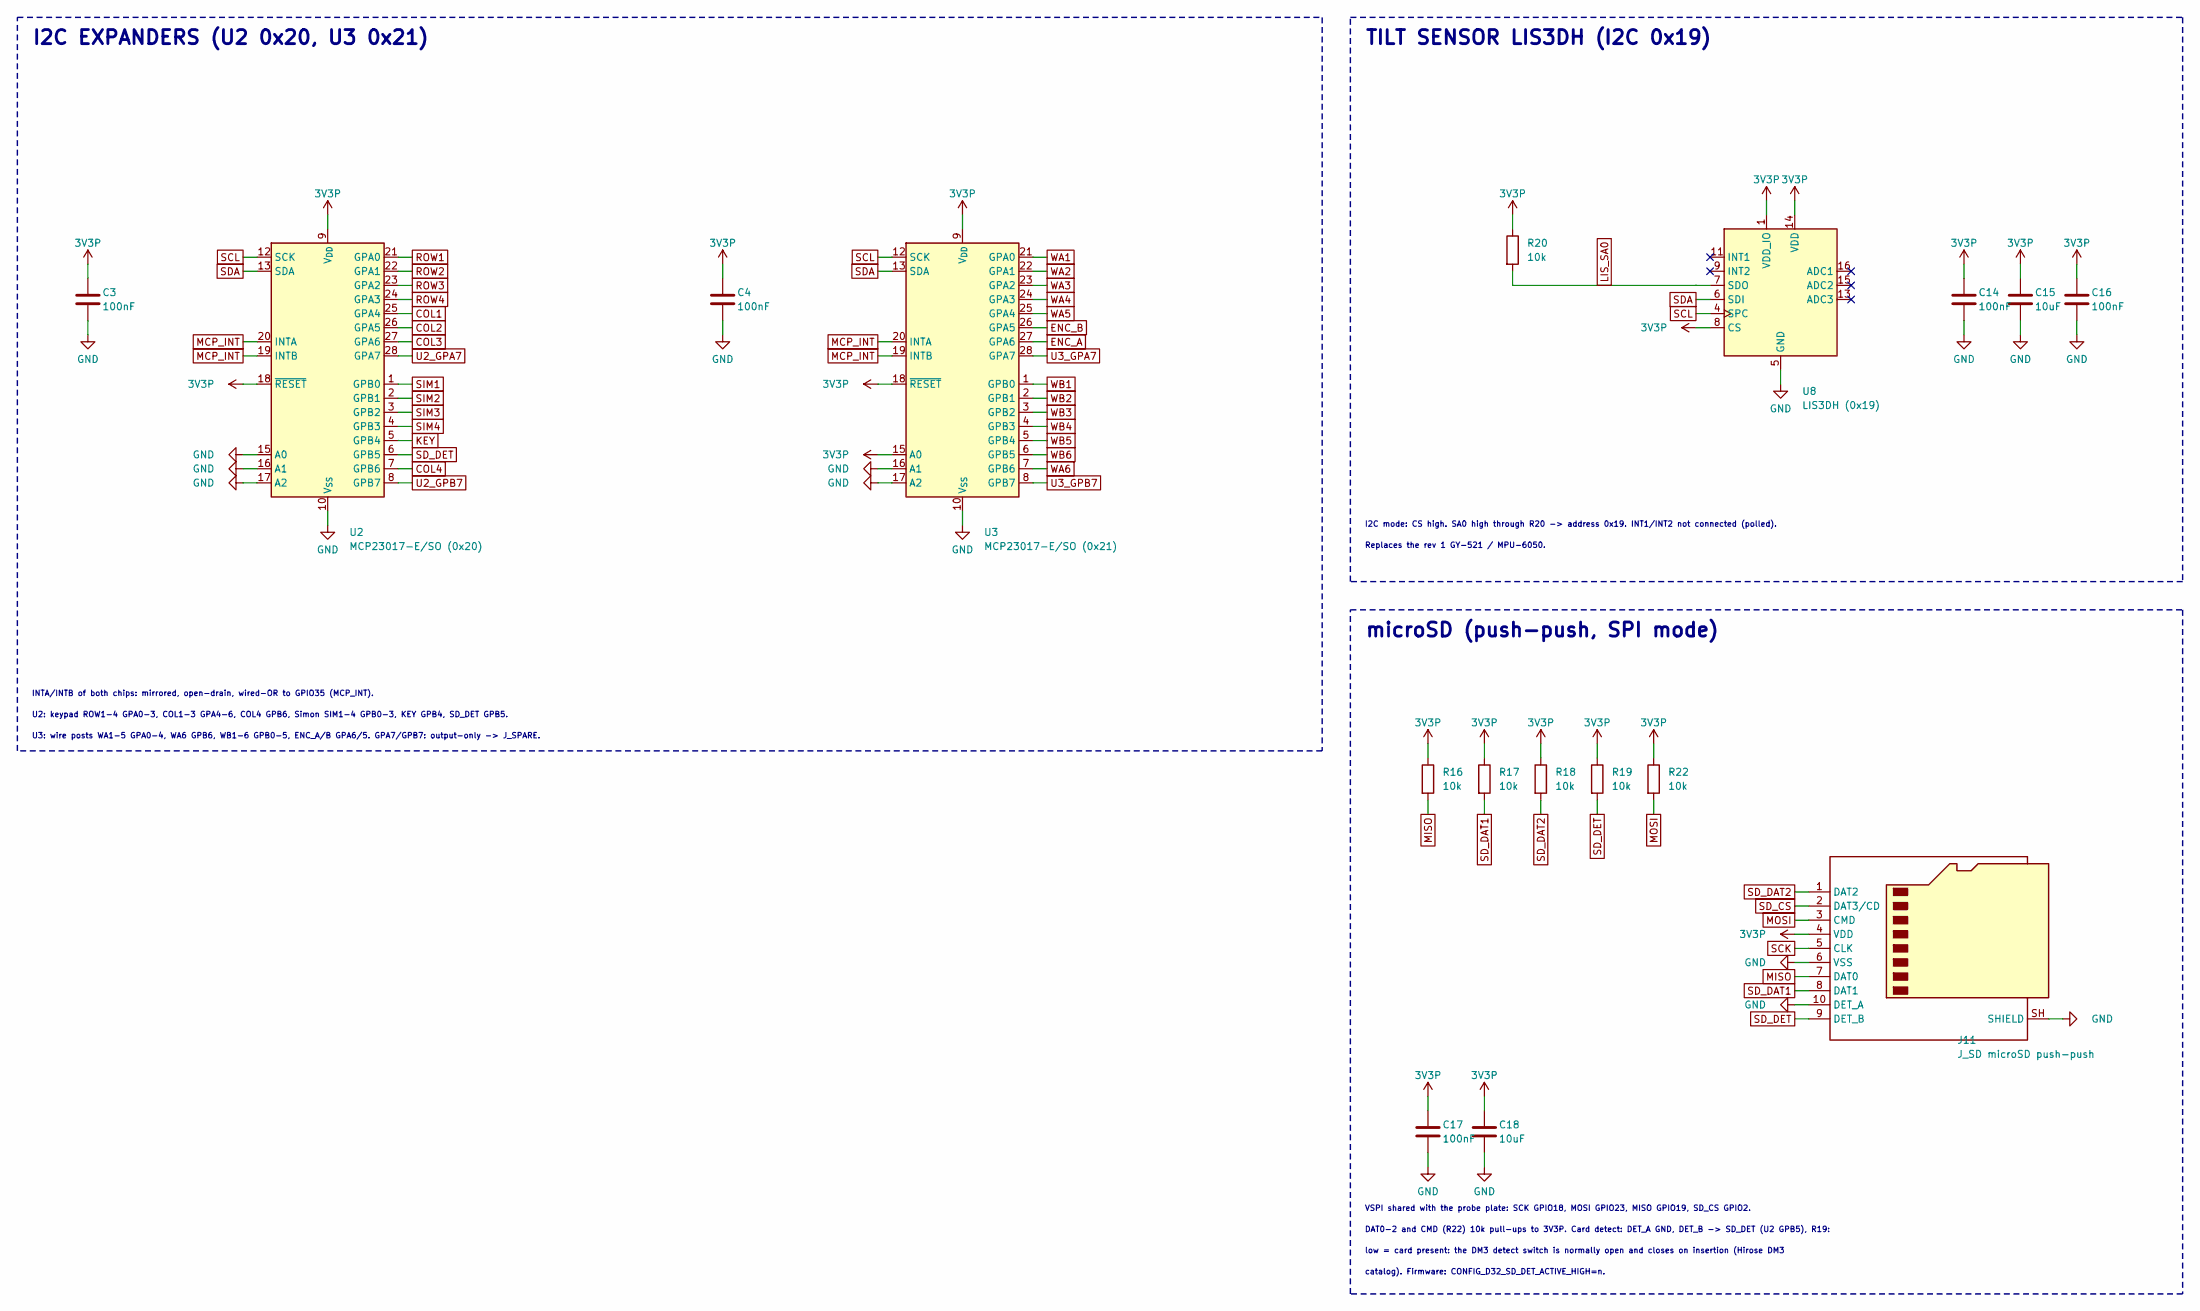
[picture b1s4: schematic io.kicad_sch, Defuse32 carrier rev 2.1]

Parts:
C3, C4, C14, C16, C17: 100nF; C_0603_1608Metric; MPN CC0603KRX7R9BB104; LCSC C14663
C15, C18: 10uF; C_0805_2012Metric; MPN CL21A106KAYNNNE; LCSC C15850
J11: J_SD microSD push-push; microSD_HC_Hirose_DM3AT-SF-PEJM5; MPN DM3AT-SF-PEJM5; LCSC C114218
R16, R17, R18, R19, R20, R22: 10k; R_0603_1608Metric; MPN 0603WAF1002T5E; LCSC C25804
U2: MCP23017-E/SO (0x20); SOIC-28W_7.5x17.9mm_P1.27mm; MPN MCP23017-E/SO; LCSC C47023
U3: MCP23017-E/SO (0x21); SOIC-28W_7.5x17.9mm_P1.27mm; MPN MCP23017-E/SO; LCSC C47023
U8: LIS3DH (0x19); LGA-16_3x3mm_P0.5mm_LayoutBorder3x5y; MPN LIS3DHTR; LCSC C15134

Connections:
3V3P: C3.1, C4.1, C14.1, C15.1, C16.1, C17.1, C18.1, J11.4 (VDD), R16.1, R17.1, R18.1, R19.1, R20.1, R22.1, U2.9 (V_{DD}), U2.18 (~RESET), U3.9 (V_{DD}), U3.15 (A0), U3.18 (~RESET), U8.1 (VDD_IO), U8.8 (CS), U8.14 (VDD); also elsewhere on the board
COL1: U2.25 (GPA4); also elsewhere on the board
COL2: U2.26 (GPA5); also elsewhere on the board
COL3: U2.27 (GPA6); also elsewhere on the board
COL4: U2.7 (GPB6); also elsewhere on the board
ENC_A: U3.27 (GPA6); also elsewhere on the board
ENC_B: U3.26 (GPA5); also elsewhere on the board
GND: C3.2, C4.2, C14.2, C15.2, C16.2, C17.2, C18.2, J11.6 (VSS), J11.10 (DET_A), J11.SH (SHIELD), U2.10 (V_{SS}), U2.15 (A0), U2.16 (A1), U2.17 (A2), U3.10 (V_{SS}), U3.16 (A1), U3.17 (A2), U8.5 (GND), U8.10 (GND), U8.12 (GND); also elsewhere on the board
KEY: U2.5 (GPB4); also elsewhere on the board
LIS_SA0: R20.2, U8.7 (SDO)
MCP_INT: U2.19 (INTB), U2.20 (INTA), U3.19 (INTB), U3.20 (INTA); also elsewhere on the board
MISO: J11.7 (DAT0), R16.2; also elsewhere on the board
MOSI: J11.3 (CMD), R22.2; also elsewhere on the board
ROW1: U2.21 (GPA0); also elsewhere on the board
ROW2: U2.22 (GPA1); also elsewhere on the board
ROW3: U2.23 (GPA2); also elsewhere on the board
ROW4: U2.24 (GPA3); also elsewhere on the board
SCK: J11.5 (CLK); also elsewhere on the board
SCL: U2.12 (SCK), U3.12 (SCK), U8.4 (SPC); also elsewhere on the board
SDA: U2.13 (SDA), U3.13 (SDA), U8.6 (SDI); also elsewhere on the board
SD_CS: J11.2 (DAT3/CD); also elsewhere on the board
SD_DAT1: J11.8 (DAT1), R17.2
SD_DAT2: J11.1 (DAT2), R18.2
SD_DET: J11.9 (DET_B), R19.2, U2.6 (GPB5)
SIM1: U2.1 (GPB0); also elsewhere on the board
SIM2: U2.2 (GPB1); also elsewhere on the board
SIM3: U2.3 (GPB2); also elsewhere on the board
SIM4: U2.4 (GPB3); also elsewhere on the board
U2_GPA7: U2.28 (GPA7); also elsewhere on the board
U2_GPB7: U2.8 (GPB7); also elsewhere on the board
U3_GPA7: U3.28 (GPA7); also elsewhere on the board
U3_GPB7: U3.8 (GPB7); also elsewhere on the board
WA1: U3.21 (GPA0); also elsewhere on the board
WA2: U3.22 (GPA1); also elsewhere on the board
WA3: U3.23 (GPA2); also elsewhere on the board
WA4: U3.24 (GPA3); also elsewhere on the board
WA5: U3.25 (GPA4); also elsewhere on the board
WA6: U3.7 (GPB6); also elsewhere on the board
WB1: U3.1 (GPB0); also elsewhere on the board
WB2: U3.2 (GPB1); also elsewhere on the board
WB3: U3.3 (GPB2); also elsewhere on the board
WB4: U3.4 (GPB3); also elsewhere on the board
WB5: U3.5 (GPB4); also elsewhere on the board
WB6: U3.6 (GPB5); also elsewhere on the board

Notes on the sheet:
I2C EXPANDERS (U2 0x20, U3 0x21)
INTA/INTB of both chips: mirrored, open-drain, wired-OR to GPIO35 (MCP_INT).
U2: keypad ROW1-4 GPA0-3, COL1-3 GPA4-6, COL4 GPB6, Simon SIM1-4 GPB0-3, KEY GPB4, SD_DET GPB5.
U3: wire posts WA1-5 GPA0-4, WA6 GPB6, WB1-6 GPB0-5, ENC_A/B GPA6/5. GPA7/GPB7: output-only -> J_SPARE.
TILT SENSOR LIS3DH (I2C 0x19)
I2C mode: CS high. SA0 high through R20 -> address 0x19. INT1/INT2 not connected (polled).
Replaces the rev 1 GY-521 / MPU-6050.
microSD (push-push, SPI mode)
VSPI shared with the probe plate: SCK GPIO18, MOSI GPIO23, MISO GPIO19, SD_CS GPIO2.
DAT0-2 and CMD (R22) 10k pull-ups to 3V3P. Card detect: DET_A GND, DET_B -> SD_DET (U2 GPB5), R19:
low = card present: the DM3 detect switch is normally open and closes on insertion (Hirose DM3
catalog). Firmware: CONFIG_D32_SD_DET_ACTIVE_HIGH=n.
